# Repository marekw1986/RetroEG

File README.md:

# RetroEG

## Overwiev
This is repository of firmware for RetroGeiger project - a Geiger counter made of retro parts. 
It uses WDC65C02 CPU and some vintage peripherals, like R65C51 UART, M6242B RTC or MC6840 timer. 
You can find description of this project on my [Hackaday.io profile](https://hackaday.io/project/167980-retrogeiger).

This project is still in development.

## Required tools
You need [cc65](https://github.com/cc65/cc65) to build this project.

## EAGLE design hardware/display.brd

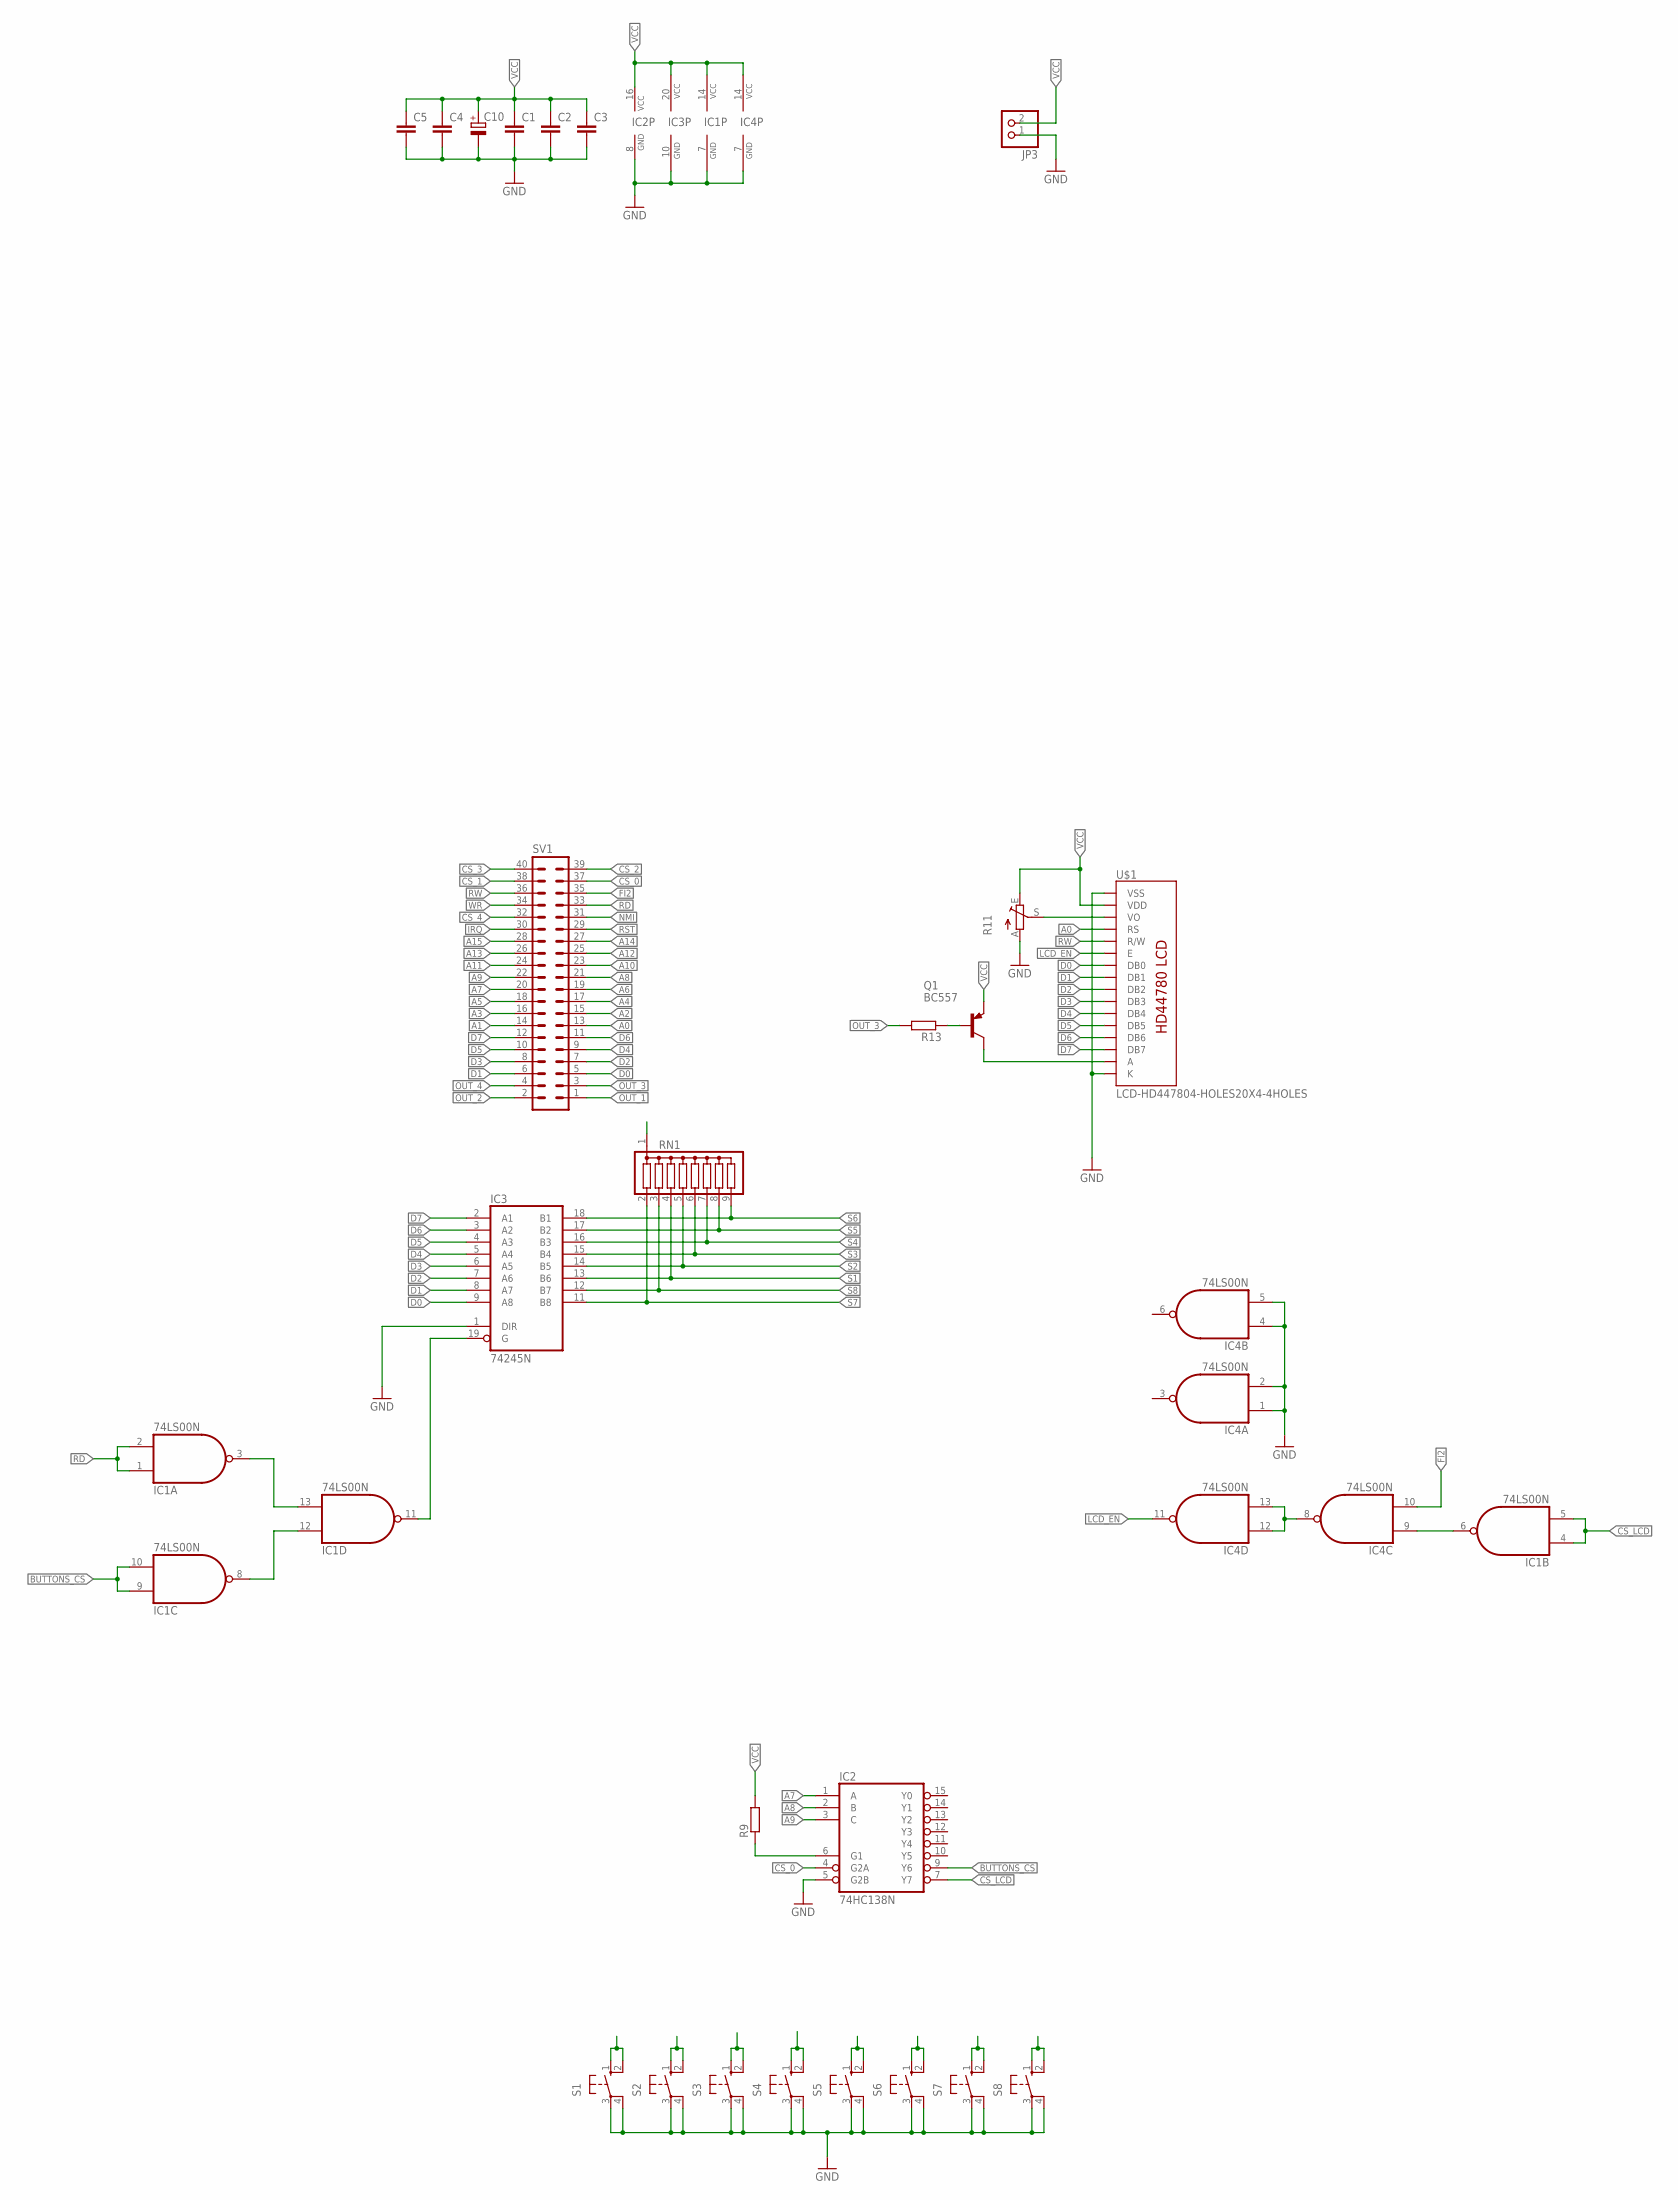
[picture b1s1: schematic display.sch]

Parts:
C1: C-EUC0603; C0603
C2, C3, C4, C5: C-EUC1206; C1206
C10: CPOL-EUE5-10.5; E5-10,5
IC1, IC4: 74LS00N; DIL14
IC2: 74HC138N; DIL16
IC3: 74245N; DIL20
JP3: PINHD-1X2/90; 1X02/90
Q1: BC557; TO92
R9, R13: R-EU_0204/7; 0204/7
R11: TRIM_EU-B25U; B25U
RN1: G08R; SIL9
S1, S2, S3, S4, S5, S6, S7, S8: 40-XX; B3F-40XX
SV1: ML40L
U$1: LCD-HD447804-HOLES20X4-4HOLES; LCD-20X4-4HOLES

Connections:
A0: SV1.13, U$1.P$4 (RS)
A1: SV1.14
A2: SV1.15
A3: SV1.16
A4: SV1.17
A5: SV1.18
A6: SV1.19
A7: IC2.1 (A), SV1.20
A8: IC2.2 (B), SV1.21
A9: IC2.3 (C), SV1.22
A10: SV1.23
A11: SV1.24
A12: SV1.25
A13: SV1.26
A14: SV1.27
A15: SV1.28
BUTTONS_CS: IC1.9 (I0), IC1.10 (I1), IC2.9 (Y6)
CS_0: IC2.4 (G2A), SV1.37
CS_1: SV1.38
CS_2: SV1.39
CS_3: SV1.40
CS_4: SV1.32
CS_LCD: IC1.4 (I0), IC1.5 (I1), IC2.7 (Y7)
D0: IC3.9 (A8), SV1.5, U$1.P$7 (DB0)
D1: IC3.8 (A7), SV1.6, U$1.P$8 (DB1)
D2: IC3.7 (A6), SV1.7, U$1.P$9 (DB2)
D3: IC3.6 (A5), SV1.8, U$1.P$10 (DB3)
D4: IC3.5 (A4), SV1.9, U$1.P$11 (DB4)
D5: IC3.4 (A3), SV1.10, U$1.P$12 (DB5)
D6: IC3.3 (A2), SV1.11, U$1.P$13 (DB6)
D7: IC3.2 (A1), SV1.12, U$1.P$14 (DB7)
FI2: IC4.10 (I1), SV1.35
GND: C1.2, C2.2, C3.2, C4.2, C5.2, C10.-, IC1.7 (GND), IC2.5 (G2B), IC2.8 (GND), IC3.1 (DIR), IC3.10 (GND), IC4.1 (I0), IC4.2 (I1), IC4.4 (I0), IC4.5 (I1), IC4.7 (GND), JP3.1, R11.A, S1.3, S1.4 (P1), S2.3, S2.4 (P1), S3.3, S3.4 (P1), S4.3, S4.4 (P1), S5.3, S5.4 (P1), S6.3, S6.4 (P1), S7.3, S7.4 (P1), S8.3, S8.4 (P1), U$1.P$1 (VSS), U$1.P$16 (K)
IRQ: SV1.30
LCD_EN: IC4.11 (O), U$1.P$6 (E)
unnamed: IC1.11 (O), IC3.19 (G)
unnamed: Q1.3 (C), U$1.P$15 (A)
unnamed: IC4.8 (O), IC4.12 (I0), IC4.13 (I1)
unnamed: IC1.6 (O), IC4.9 (I0)
unnamed: Q1.2 (B), R13.1
unnamed: IC1.3 (O), IC1.13 (I1)
unnamed: IC1.8 (O), IC1.12 (I0)
unnamed: IC2.6 (G1), R9.1
unnamed: R11.S, U$1.P$3 (VO)
NMI: SV1.31
OUT_1: SV1.1
OUT_2: SV1.2
OUT_3: R13.2, SV1.3
OUT_4: SV1.4
RD: IC1.1 (I0), IC1.2 (I1), SV1.33
RST: SV1.29
RW: SV1.36, U$1.P$5 (R/W)
S1: IC3.13 (B6), RN1.4, S1.1 (S), S1.2 (S1)
S2: IC3.14 (B5), RN1.5, S2.1 (S), S2.2 (S1)
S3: IC3.15 (B4), RN1.6, S3.1 (S), S3.2 (S1)
S4: IC3.16 (B3), RN1.7, S4.1 (S), S4.2 (S1)
S5: IC3.17 (B2), RN1.8, S5.1 (S), S5.2 (S1)
S6: IC3.18 (B1), RN1.9, S6.1 (S), S6.2 (S1)
S7: IC3.11 (B8), RN1.2, S7.1 (S), S7.2 (S1)
S8: IC3.12 (B7), RN1.3, S8.1 (S), S8.2 (S1)
VCC: C1.1, C2.1, C3.1, C4.1, C5.1, C10.+, IC1.14 (VCC), IC2.16 (VCC), IC3.20 (VCC), IC4.14 (VCC), JP3.2, Q1.1 (E), R9.2, R11.E, RN1.1, U$1.P$2 (VDD)
WR: SV1.34

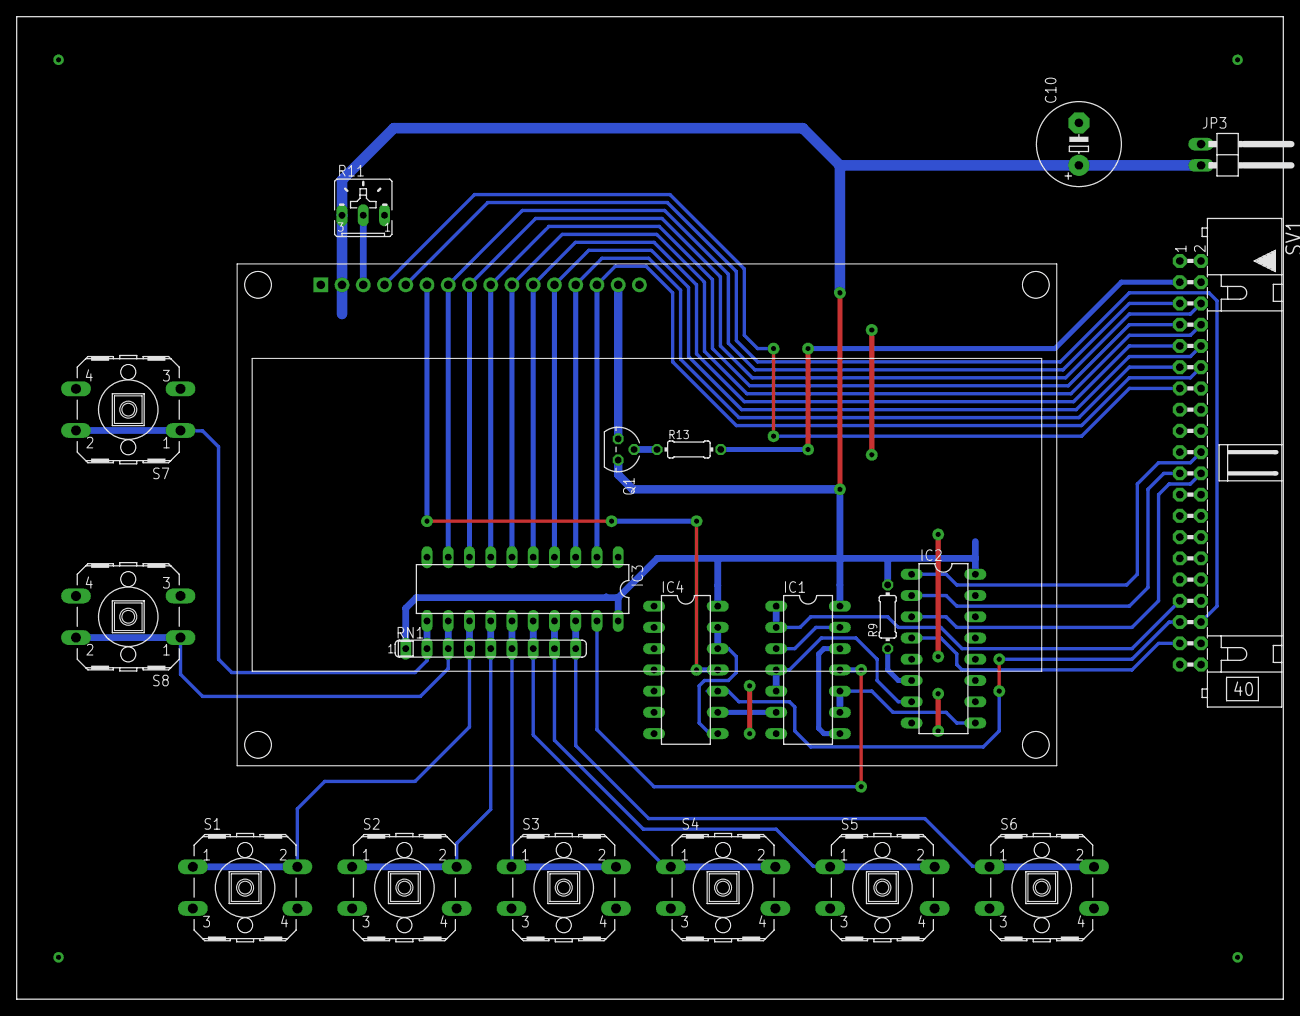
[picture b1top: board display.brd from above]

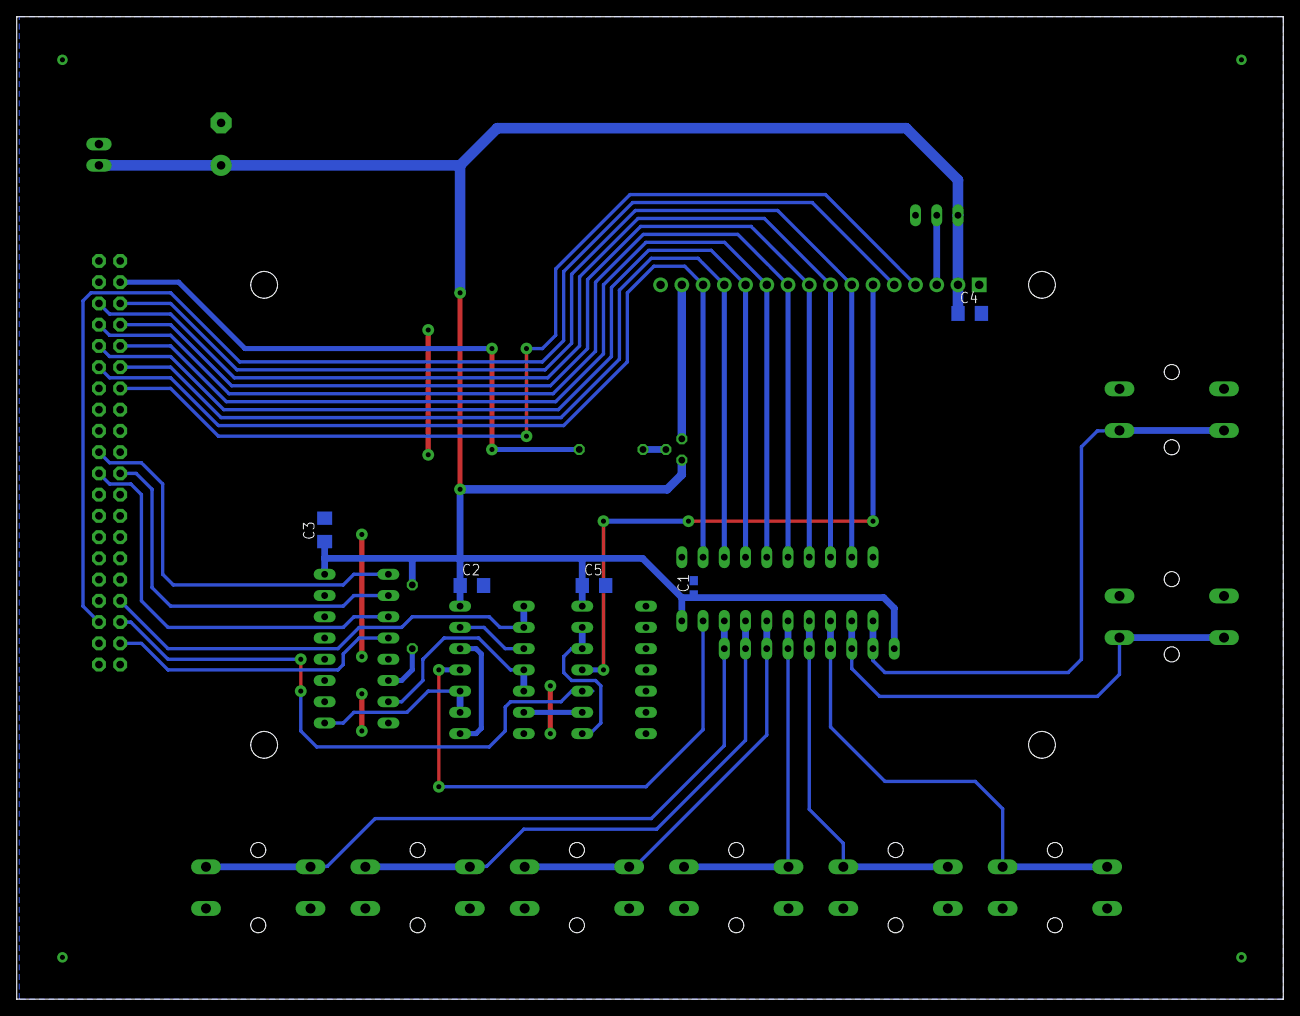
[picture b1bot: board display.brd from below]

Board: 2 copper layers, 151.4 x 117.5 mm, 26 parts (5 on the bottom side), 39 nets.

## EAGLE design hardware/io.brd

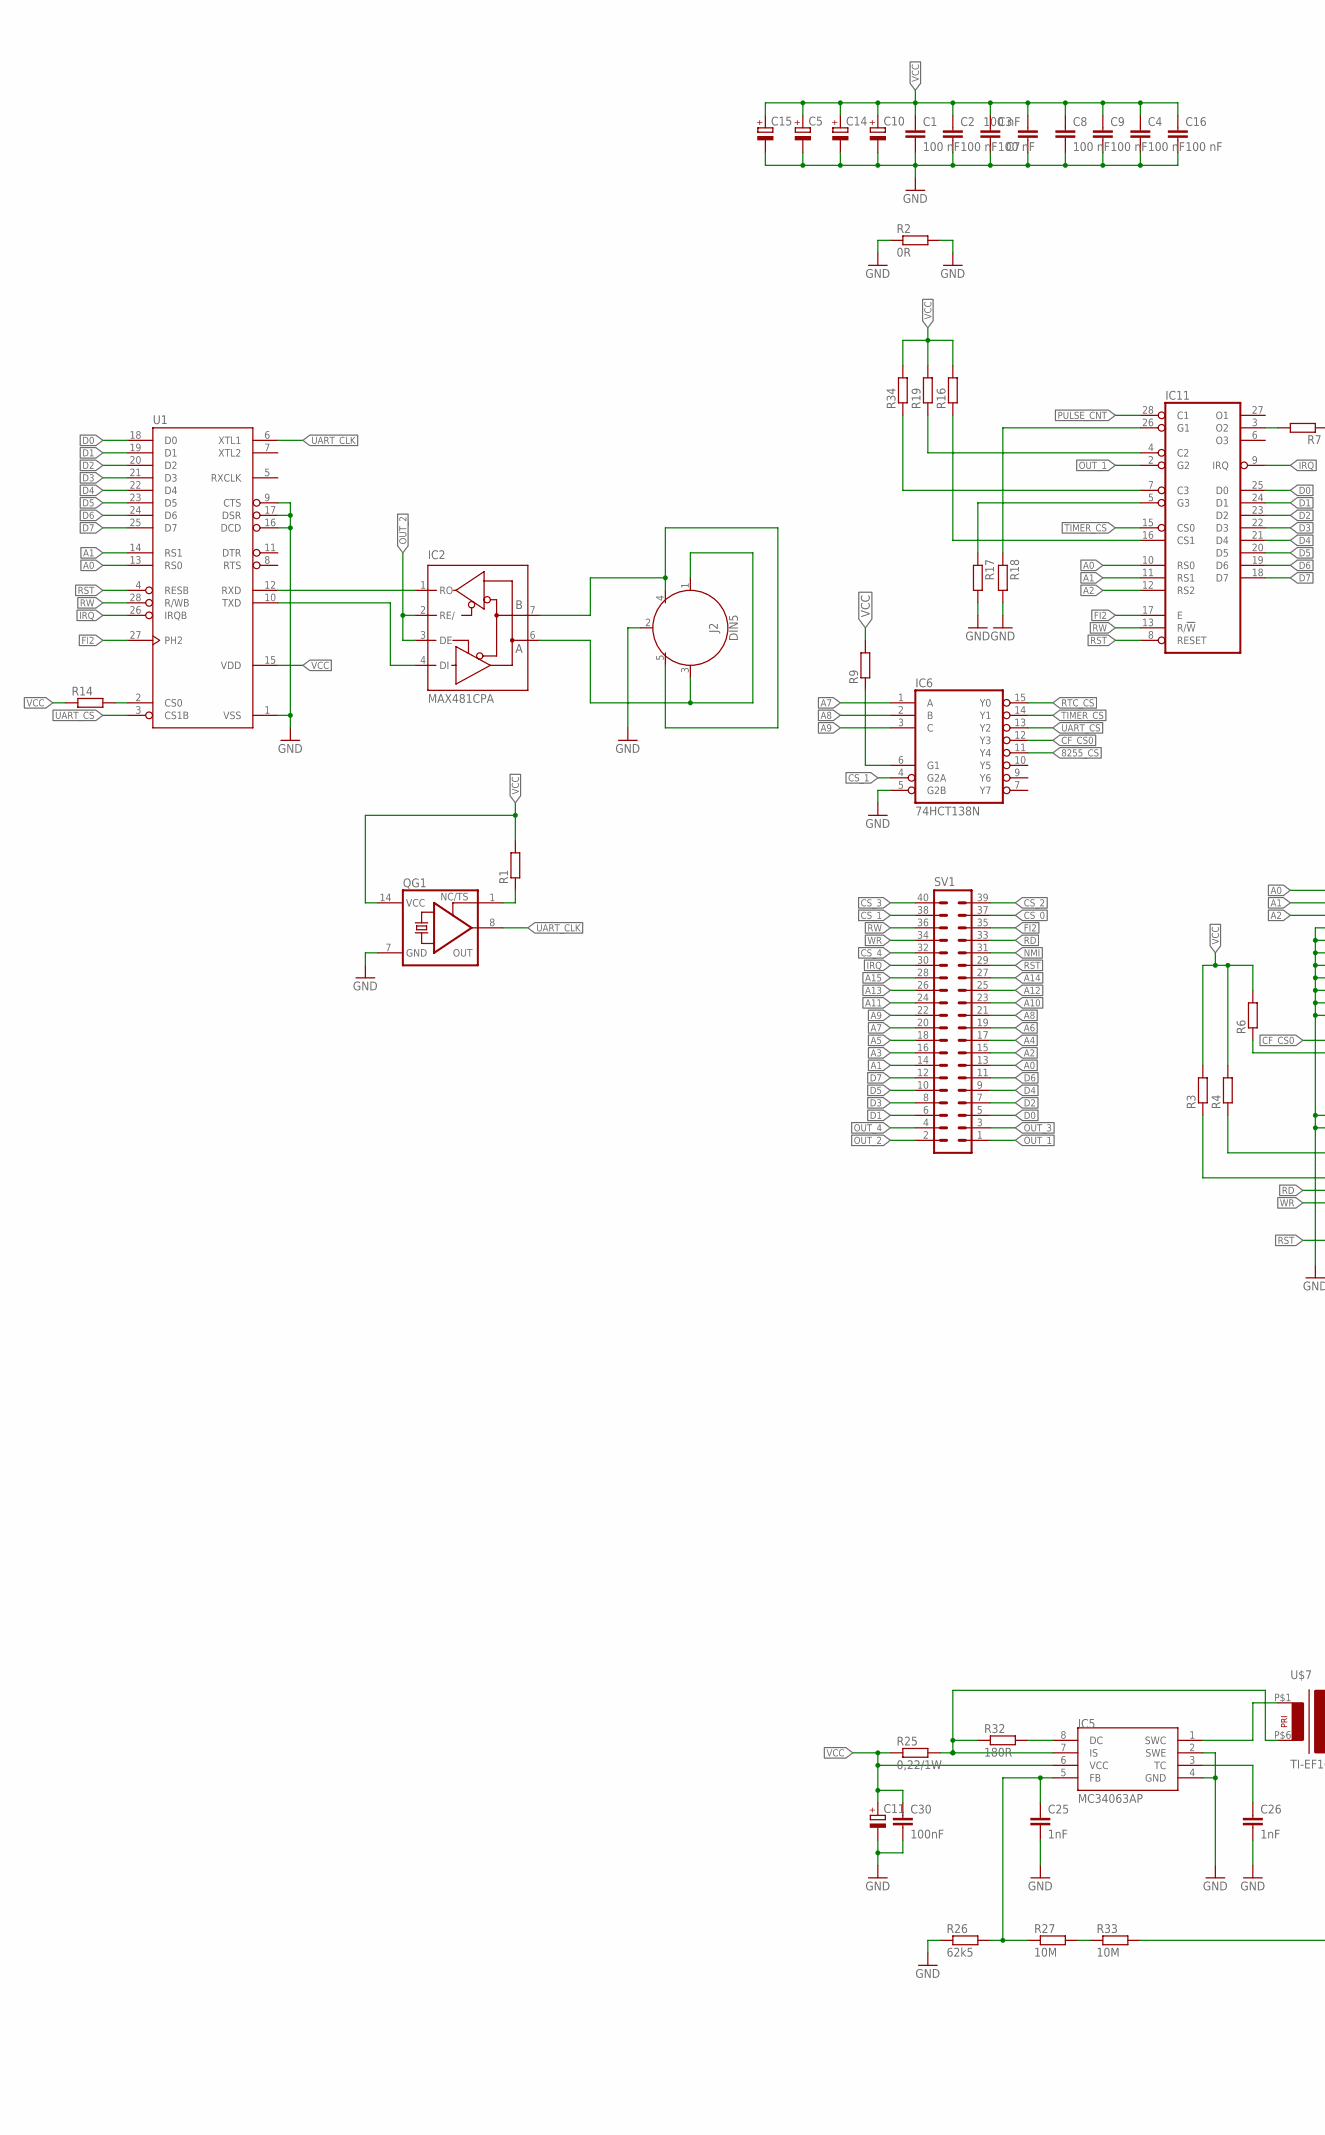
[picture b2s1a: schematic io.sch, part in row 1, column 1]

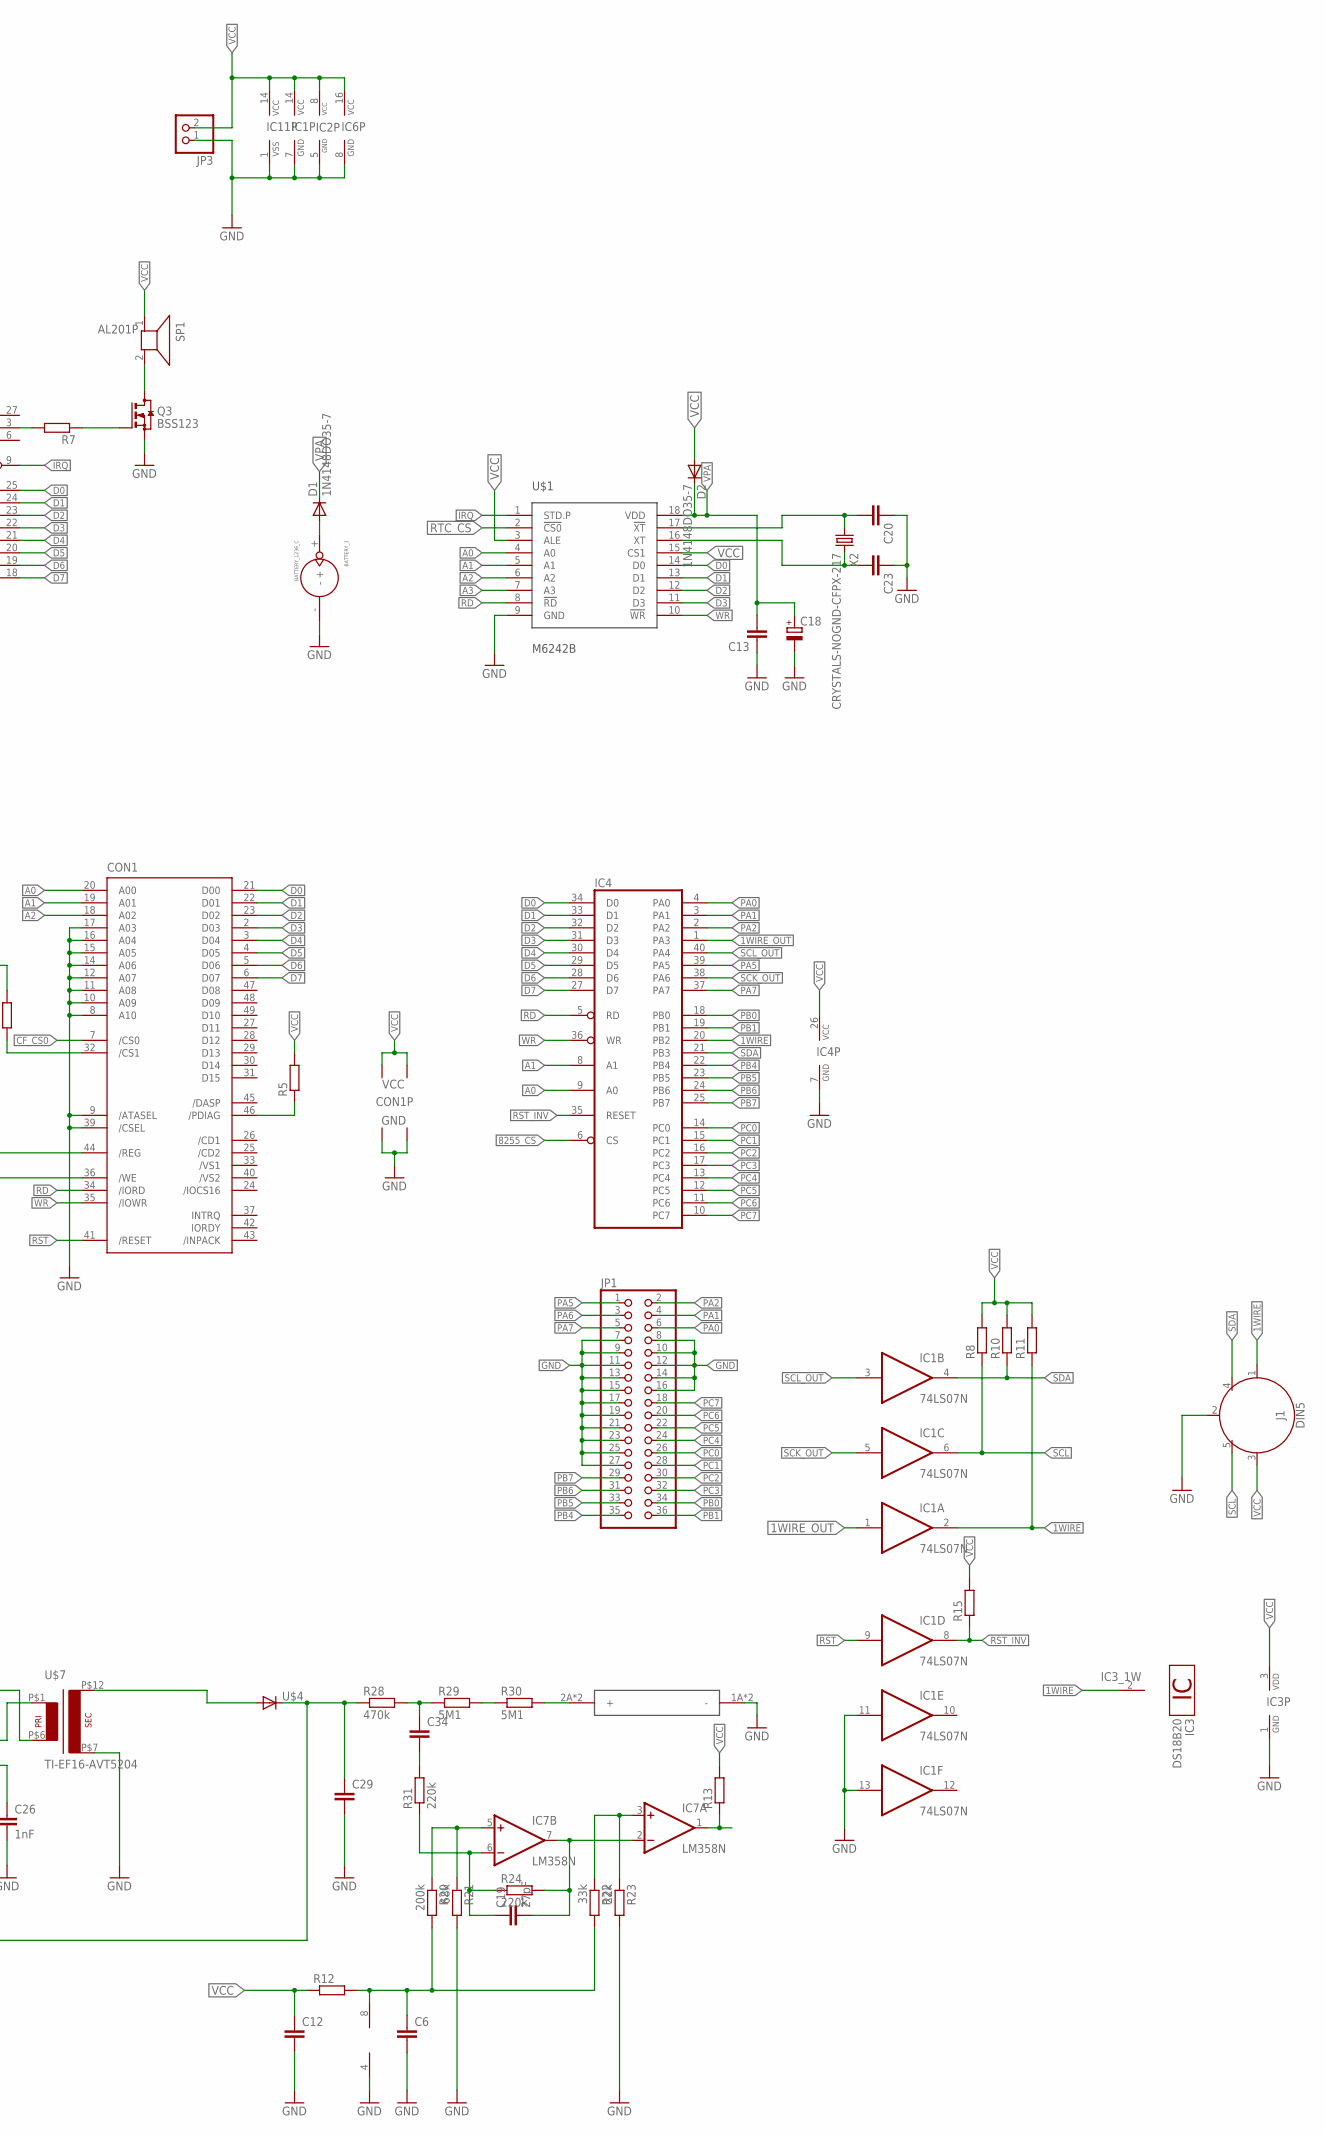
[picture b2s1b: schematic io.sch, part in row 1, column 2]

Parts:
BATTERY_1: BATTERY_1236_C
C1, C2, C3, C8, C9: 100 nF; C1206
C4, C7, C16: 100 nF; C0603
C5: CPOL-EUSMCC; SMC_C
C6, C12, C13, C20, C23: C-EUC0603; C0603
C10, C15: CPOL-EUE5-10.5; E5-10,5
C11: CPOL-EUSMCE; SMC_E
C14: CPOL-EUE3.5-8; E3,5-8
C18: CPOL-EUSMCB; SMC_B
C19: 27pF; C0603
C25, C26: 1nF; C0603
C29: C-EU225-113X268; C225-113X268
C30: 100nF; C0603
C34: C-EU050-024X044; C050-024X044
CON1: CF-CARD-IDE_MODE; MI20-50PD-SF
D1, D2: 1N4148DO35-7; DO35-7
IC1: 74LS07N; DIL14
IC2: MAX481CPA; DIL08
IC3: DS18B20; TO92-
IC4: 8255A; DIL40
IC5: MC34063AP; DIL08
IC6: 74HCT138N; DIL16
IC7: LM358N; DIL08
IC11: 6840; DIL28
J1, J2: DIN5; DIN5-RA-PTH
JP1: PINHD-2X18; 2X18
JP3: PINHD-1X2/90; 1X02/90
Q3: BSS123; SOT23
QG1: XO-14; DIL14S
R1, R9: R-EU_R1206; R1206
R2: 0R; M1206
R3, R4, R5, R6, R13, R14, R15, R18, R34: R-EU_R0603; R0603
R7, R19: R-EU_0204/5; 0204/5
R8, R10, R11, R12, R17: R-EU_0204/7; 0204/7
R16: R-EU_R0402; R0402
R20: 200k; R0603
R21: 68k; R0603
R22: 33k; R0603
R23: 22k; R0603
R24: 220k; R0603
R25: 0,22/1W; R2010
R26: 62k5; R1206
R27, R33: 10M; 0204/7
R28: 470k; R2512
R29, R30: 5M1; R2512
R31: 220k; 0204/7
R32: 180R; R0805
SP1: AL201P
SV1: ML40L
U1: G65SC51P; DIP-28
U$1: M6242B; DIL18
U$4: DIODE-MELF-MLL41; MELF-MLL41
U$5: STS5; GEIGERTUBE
U$7: TI-EF16-AVT5204; EF16-K-H-12P-12,5
X2: CRYSTALS-NOGND-CFPX-217; 3.2X1.5-2-PAD

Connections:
1WIRE: IC1.2 (O), IC3.2 (1W), IC4.20 (PB2), J1.1, R11.1
1WIRE_OUT: IC1.1 (I), IC4.1 (PA3)
8255_CS: IC4.6 (CS), IC6.11 (Y4)
A0: CON1.20 (A00), IC4.9 (A0), IC11.10 (RS0), SV1.13, U1.13 (RS0), U$1.4 (A0)
A1: CON1.19 (A01), IC4.8 (A1), IC11.11 (RS1), SV1.14, U1.14 (RS1), U$1.5 (A1)
A2: CON1.18 (A02), IC11.12 (RS2), SV1.15, U$1.6 (A2)
A3: SV1.16, U$1.7 (A3)
A4: SV1.17
A5: SV1.18
A6: SV1.19
A7: IC6.1 (A), SV1.20
A8: IC6.2 (B), SV1.21
A9: IC6.3 (C), SV1.22
A10: SV1.23
A11: SV1.24
A12: SV1.25
A13: SV1.26
A14: SV1.27
A15: SV1.28
A_3V: C6.1, IC7.8 (V+), R12.2, R20.2, R22.2
CF_CS0: CON1.7 (/CS0), IC6.12 (Y3)
CS_0: SV1.37
CS_1: IC6.4 (G2A), SV1.38
CS_2: SV1.39
CS_3: SV1.40
CS_4: SV1.32
D0: CON1.21 (D00), IC4.34 (D0), IC11.25 (D0), SV1.5, U1.18 (D0), U$1.14 (D0)
D1: CON1.22 (D01), IC4.33 (D1), IC11.24 (D1), SV1.6, U1.19 (D1), U$1.13 (D1)
D2: CON1.23 (D02), IC4.32 (D2), IC11.23 (D2), SV1.7, U1.20 (D2), U$1.12 (D2)
D3: CON1.2 (D03), IC4.31 (D3), IC11.22 (D3), SV1.8, U1.21 (D3), U$1.11 (D3)
D4: CON1.3 (D04), IC4.30 (D4), IC11.21 (D4), SV1.9, U1.22 (D4)
D5: CON1.4 (D05), IC4.29 (D5), IC11.20 (D5), SV1.10, U1.23 (D5)
D6: CON1.5 (D06), IC4.28 (D6), IC11.19 (D6), SV1.11, U1.24 (D6)
D7: CON1.6 (D07), IC4.27 (D7), IC11.18 (D7), SV1.12, U1.25 (D7)
FI2: IC11.17 (E), SV1.35, U1.27 (PH2)
GND: BATTERY_1.-, C1.2, C2.2, C3.2, C4.2, C5.-, C6.2, C7.1, C8.2, C9.2, C10.-, C11.-, C12.2, C13.1, C14.-, C15.-, C16.2, C18.-, C20.1, C23.1, C25.2, C26.2, C29.2, C30.2, CON1.1 (GND1), CON1.8 (A10), CON1.9 (/ATASEL), CON1.10 (A09), CON1.11 (A08), CON1.12 (A07), CON1.14 (A06), CON1.15 (A05), CON1.16 (A04), CON1.17 (A03), CON1.39 (/CSEL), CON1.50 (GND2), IC1.7 (GND), IC1.11 (I), IC1.13 (I), IC2.5 (GND), IC3.1 (GND), IC4.7 (GND), IC5.2 (SWE), IC5.4 (GND), IC6.5 (G2B), IC6.8 (GND), IC7.4 (V-), IC11.1 (VSS), J1.2, J2.2, JP1.7, JP1.8, JP1.9, JP1.10, JP1.11, JP1.12, JP1.13, JP1.14, JP1.15, JP1.16, JP1.17, JP1.19, JP1.21, JP1.23, JP1.25, JP1.27, JP3.1, Q3.2 (S), QG1.7 (GND), R2.1, R2.2, R17.2, R18.2, R21.2, R23.2, R26.1, U1.1 (VSS), U1.9 (CTS), U1.16 (DCD), U1.17 (DSR), U$1.9 (GND), U$5.1A (-), U$5.1B (-), U$7.P$7 (P7)
HV: C29.1, R28.1, R33.2, U$4.C
IRQ: IC11.9 (IRQ), SV1.30, U1.26 (IRQB), U$1.1 (STD.P)
unnamed: QG1.1 (TS), R1.1
unnamed: C19.1, IC7.6 (-IN), R24.1, R31.1
unnamed: IC5.7 (IS), R25.2, R32.1, U$7.P$6 (P6)
unnamed: U$4.A, U$7.P$12 (P12)
unnamed: C26.1, IC5.3 (TC)
unnamed: C25.1, IC5.5 (FB), R26.2, R27.1
unnamed: R30.2, U$5.2A (+), U$5.2B (+)
unnamed: IC11.3 (O2), R7.2
unnamed: CON1.32 (/CS1), R6.1
unnamed: Q3.3 (D), SP1.2
unnamed: C19.2, IC7.2 (-IN), IC7.7 (OUT), R24.2
unnamed: IC6.6 (G1), R9.1
unnamed: CON1.44 (/REG), R4.1
unnamed: CON1.36 (/WE), R3.1
unnamed: CON1.46 (/PDIAG), R5.1
unnamed: BATTERY_1.+, D1.A
unnamed: R29.2, R30.1
unnamed: C34.1, R28.2, R29.1
unnamed: C34.2, R31.2
unnamed: IC7.5 (+IN), R20.1, R21.1
unnamed: IC7.3 (+IN), R22.1, R23.1
unnamed: R14.2, U1.2 (CS0)
unnamed: IC11.16 (CS1), R16.1
unnamed: IC5.1 (SWC), U$7.P$1 (P1)
unnamed: IC5.8 (DC), R32.2
unnamed: R27.2, R33.1
unnamed: IC11.5 (G3), R17.1
unnamed: IC11.26 (G1), R18.1
unnamed: IC11.4 (C2), R19.1
unnamed: IC11.7 (C3), R34.1
NMI: SV1.31
OUT_1: IC11.2 (G2), SV1.1
OUT_2: IC2.2 (RE/), IC2.3 (DE), SV1.2
OUT_3: SV1.3
OUT_4: SV1.4
PA0: IC4.4 (PA0), JP1.6
PA1: IC4.3 (PA1), JP1.4
PA2: IC4.2 (PA2), JP1.2
PA5: IC4.39 (PA5), JP1.1
PA6: JP1.3
PA7: IC4.37 (PA7), JP1.5
PB0: IC4.18 (PB0), JP1.34
PB1: IC4.19 (PB1), JP1.36
PB4: IC4.22 (PB4), JP1.35
PB5: IC4.23 (PB5), JP1.33
PB6: IC4.24 (PB6), JP1.31
PB7: IC4.25 (PB7), JP1.29
PC0: IC4.14 (PC0), JP1.26
PC1: IC4.15 (PC1), JP1.28
PC2: IC4.16 (PC2), JP1.30
PC3: IC4.17 (PC3), JP1.32
PC4: IC4.13 (PC4), JP1.24
PC5: IC4.12 (PC5), JP1.22
PC6: IC4.11 (PC6), JP1.20
PC7: IC4.10 (PC7), JP1.18
PULSE_CNT: IC7.1 (OUT), IC11.28 (C1), R13.1
RD: CON1.34 (/IORD), IC4.5 (RD), SV1.33, U$1.8 (!RD)
RST: CON1.41 (/RESET), IC1.9 (I), IC11.8 (RESET), SV1.29, U1.4 (RESB)
RST_INV: IC1.8 (O), IC4.35 (RESET), R15.1
RTC_CS: IC6.15 (Y0), U$1.2 (!CS0)
RW: IC11.13 (R/!W), SV1.36, U1.28 (R/WB)
RXD: IC2.1 (RO), U1.12 (RXD)
RX_A: IC2.6 (A), J2.1, J2.3
RX_B: IC2.7 (B), J2.4, J2.5
SCK_OUT: IC1.5 (I), IC4.38 (PA6)
SCL: IC1.6 (O), J1.5, R8.1
SCL_OUT: IC1.3 (I), IC4.40 (PA4)
SDA: IC1.4 (O), IC4.21 (PB3), J1.4, R10.1
SOSCI: C20.2, U$1.17 (!XT), X2.1
SOSCO: C23.2, U$1.16 (XT), X2.2
TICK: Q3.1 (G), R7.1
TIMER_CS: IC6.14 (Y1), IC11.15 (CS0)
TXD: IC2.4 (DI), U1.10 (TXD)
UART_CLK: QG1.8 (OUT), U1.6 (XTL1)
UART_CS: IC6.13 (Y2), U1.3 (CS1B)
VCC: C1.1, C2.1, C3.1, C4.1, C5.+, C7.2, C8.1, C9.1, C10.+, C11.+, C12.1, C14.+, C15.+, C16.1, C30.1, CON1.13 (VCC2), CON1.38 (VCC1), D2.A, IC1.14 (VCC), IC2.8 (VCC), IC3.3 (VDD), IC4.26 (VCC), IC5.6 (VCC), IC6.16 (VCC), IC11.14 (VCC), J1.3, JP3.2, QG1.14 (VCC), R1.2, R3.2, R4.2, R5.2, R6.2, R8.2, R9.2, R10.2, R11.2, R12.1, R13.2, R14.1, R15.2, R16.2, R19.2, R25.1, R34.2, SP1.1, U1.15 (VDD), U$1.3 (ALE), U$1.15 (CS1)
VPA: C13.2, C18.+, D1.C, D2.C, U$1.18 (VDD)
WR: CON1.35 (/IOWR), IC4.36 (WR), SV1.34, U$1.10 (!WR)

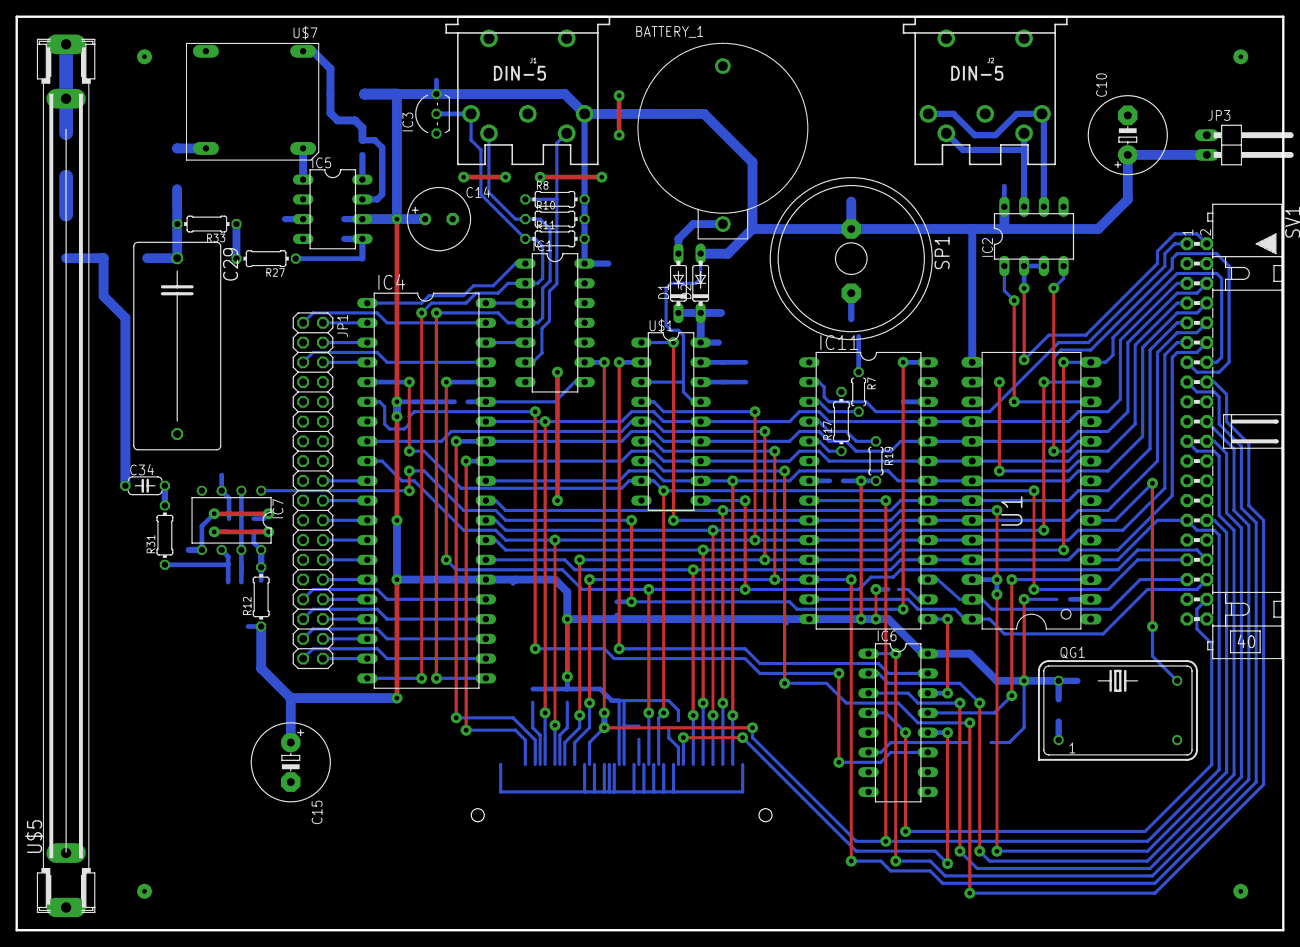
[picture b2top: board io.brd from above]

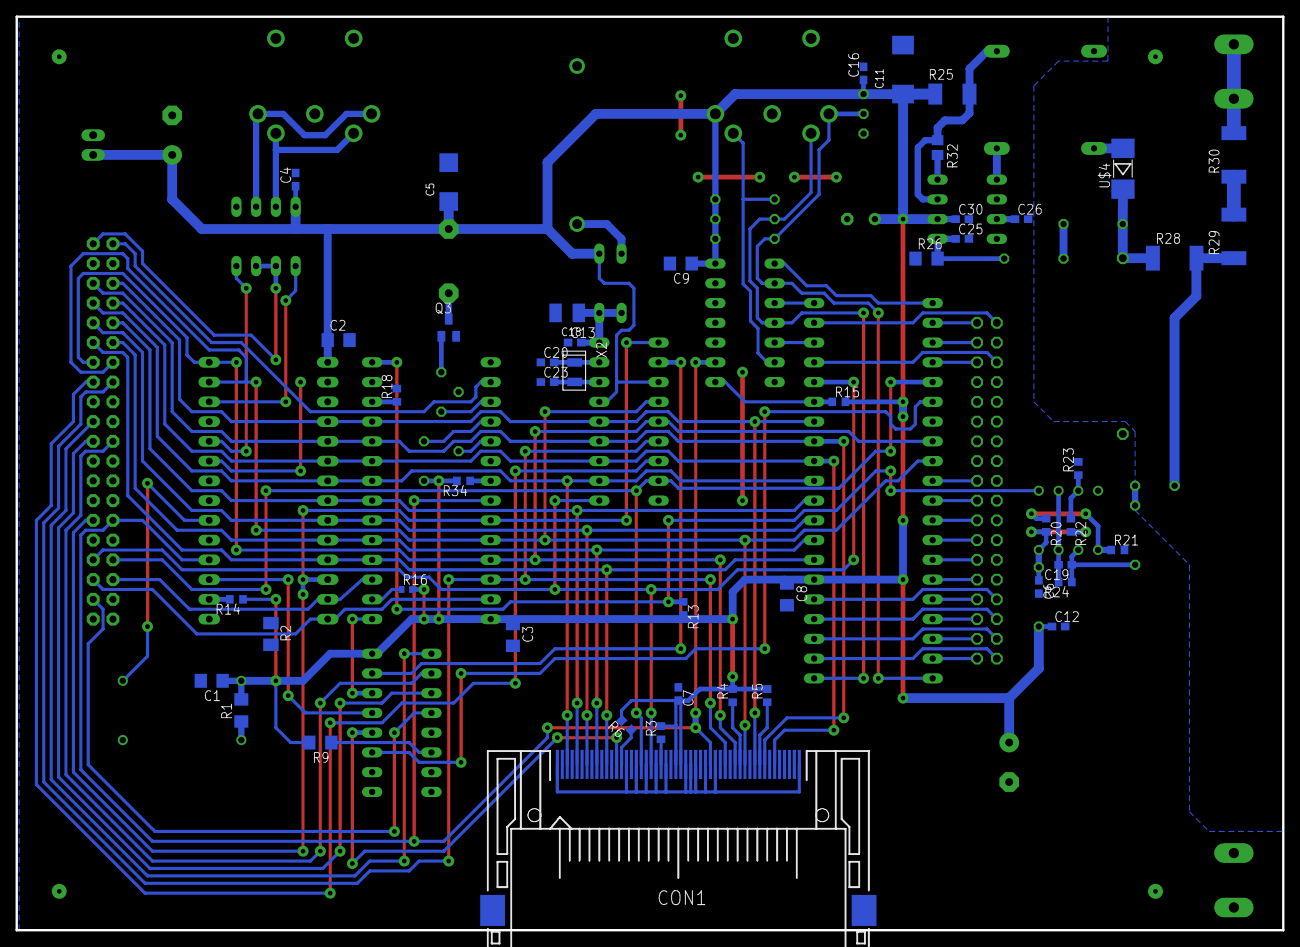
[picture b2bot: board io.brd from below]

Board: 2 copper layers, 162.9 x 117.5 mm, 85 parts (48 on the bottom side), 99 nets.

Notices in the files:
parts and their libraries:
SparkFun-Connectors: Licensing: Creative Commons ShareAlike 4.0 International - https://creativecommons.org/licenses/by-sa/4.0
